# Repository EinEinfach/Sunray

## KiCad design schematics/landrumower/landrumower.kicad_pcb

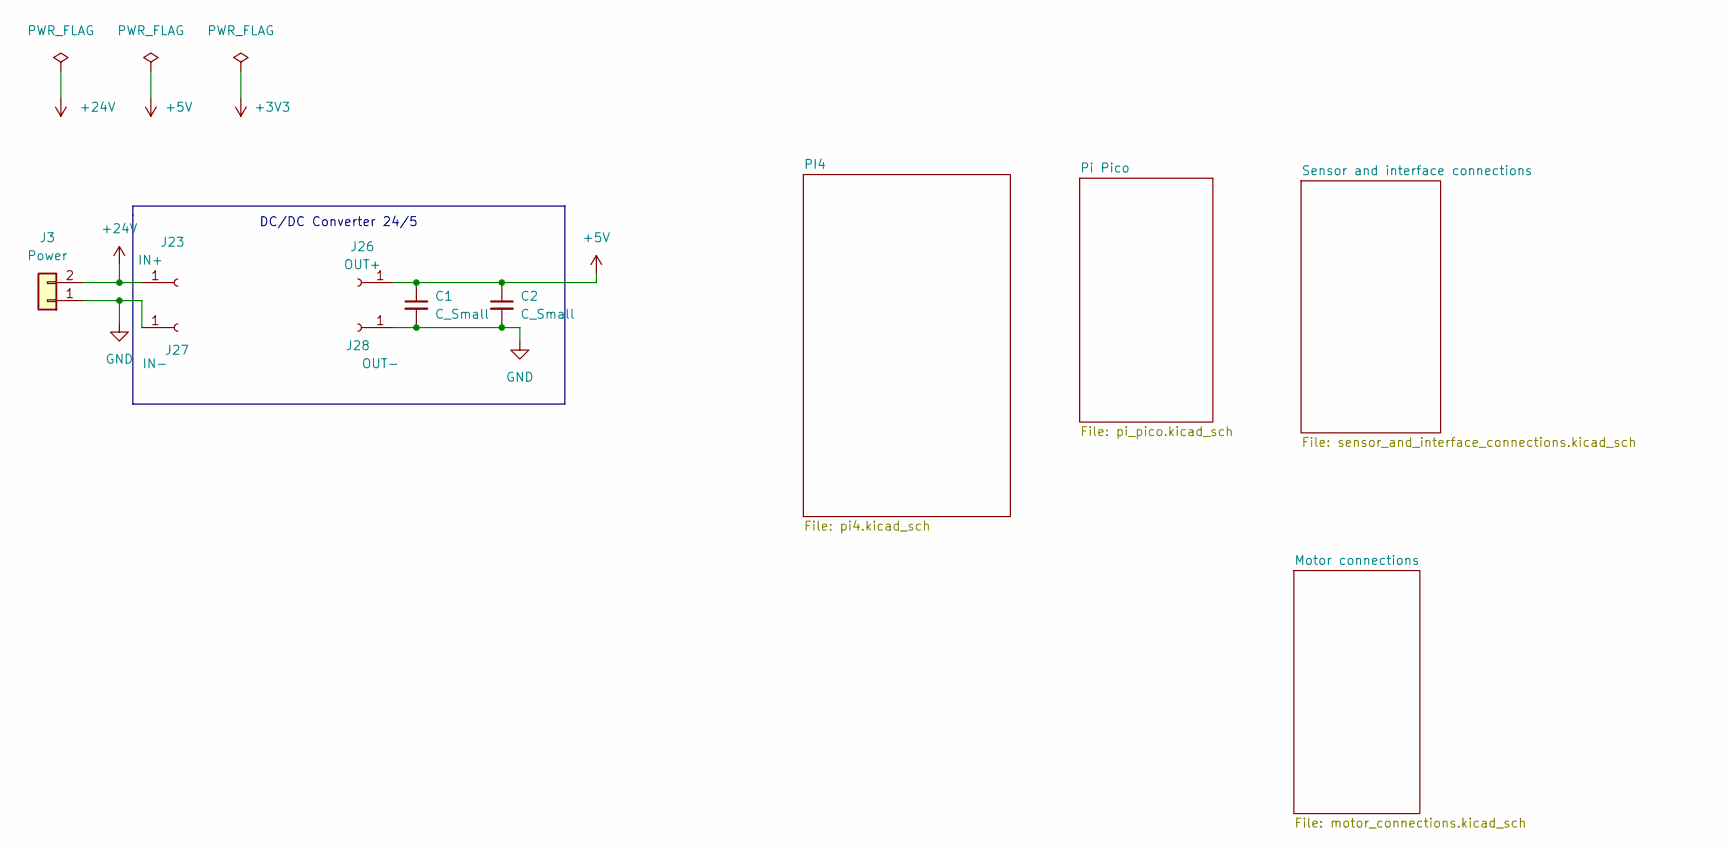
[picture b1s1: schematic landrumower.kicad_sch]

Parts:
C1, C2: C_Small; C_0805_2012Metric_Pad1.18x1.45mm_HandSolder
J3: Power; TerminalBlock_Altech_AK300-2_P5.00mm
J23: IN+; PinSocket_1x01_P2.54mm_Vertical
J26: OUT+; PinSocket_1x01_P2.54mm_Vertical
J27: IN-; PinSocket_1x01_P2.54mm_Vertical
J28: OUT-; PinSocket_1x01_P2.54mm_Vertical

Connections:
+5V: C1.1, C2.1, J26.1; also elsewhere on the board
+24V: J3.2, J23.1
GND: C1.2, C2.2, J3.1, J27.1, J28.1; also elsewhere on the board

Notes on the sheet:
DC/DC Converter 24/5

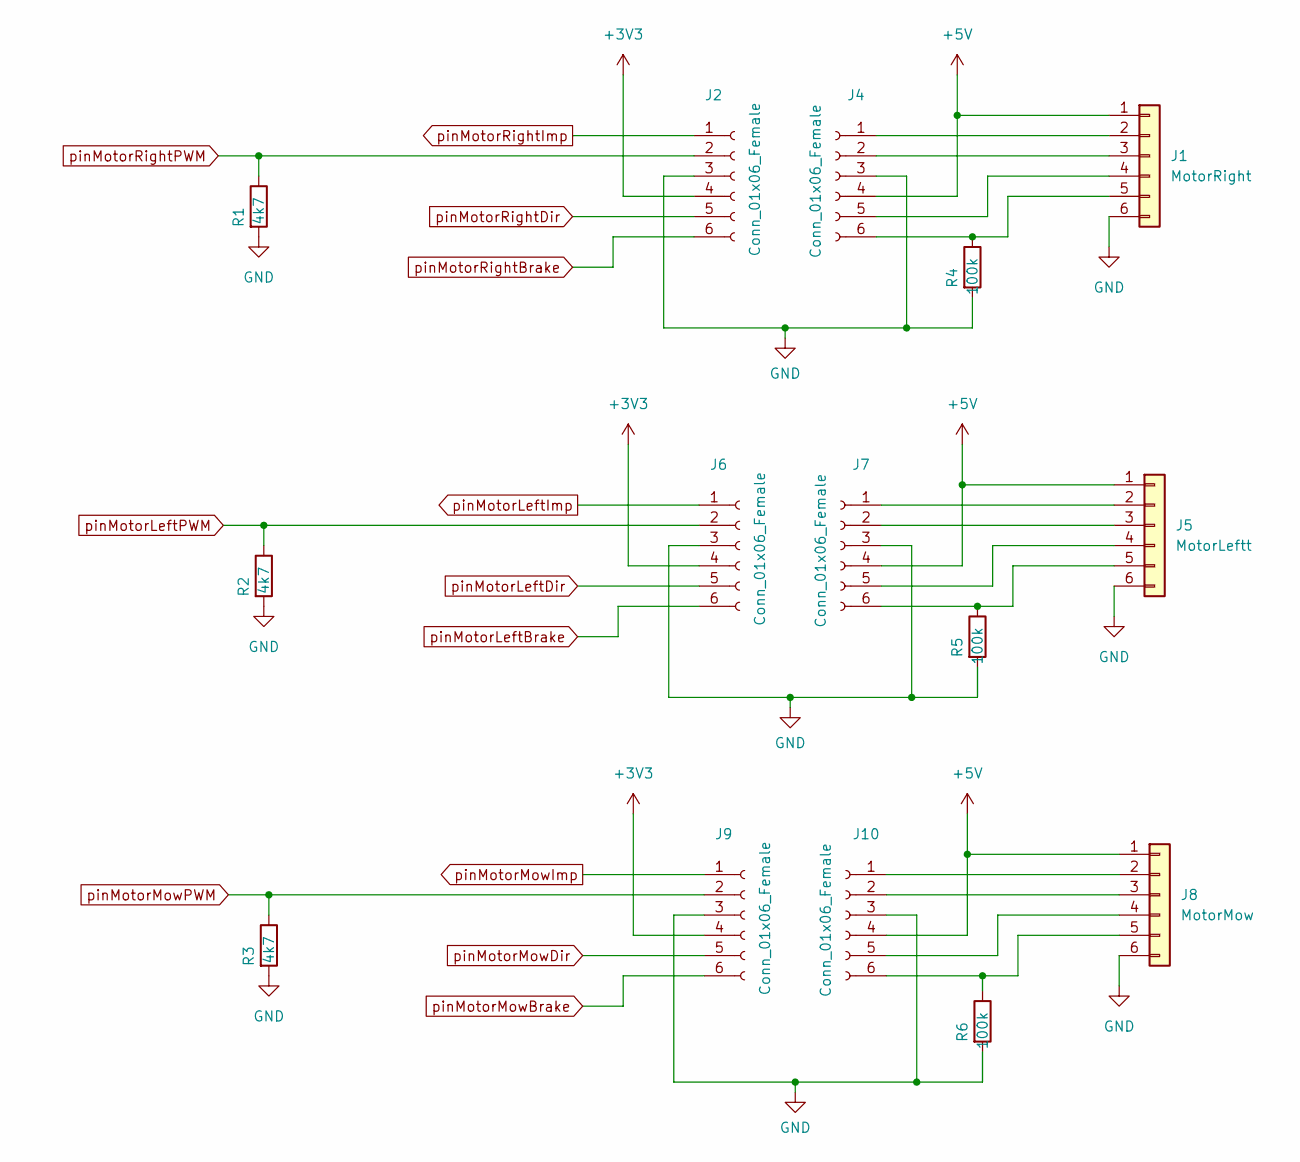
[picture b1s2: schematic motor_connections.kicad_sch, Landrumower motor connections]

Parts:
J1: MotorRight; JST_EH_B6B-EH-A_1x06_P2.50mm_Vertical
J2, J4, J6, J7, J9, J10: Conn_01x06_Female; PinSocket_1x06_P2.54mm_Vertical
J5: MotorLeftt; JST_EH_B6B-EH-A_1x06_P2.50mm_Vertical
J8: MotorMow; JST_EH_B6B-EH-A_1x06_P2.50mm_Vertical
R1, R2, R3: 4k7; R_0805_2012Metric_Pad1.20x1.40mm_HandSolder
R4, R5, R6: 100k; R_0805_2012Metric_Pad1.20x1.40mm_HandSolder

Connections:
+3V3: J2.4, J6.4, J9.4; also elsewhere on the board
+5V: J1.1, J4.4, J5.1, J7.4, J8.1, J10.4; also elsewhere on the board
GND: J1.6, J2.3, J4.3, J5.6, J6.3, J7.3, J8.6, J9.3, J10.3, R1.2, R2.2, R3.2, R4.2, R5.2, R6.2; also elsewhere on the board
unnamed: J1.2, J4.1
unnamed: J1.3, J4.2
unnamed: J1.4, J4.5
unnamed: J1.5, J4.6, R4.1
unnamed: J5.2, J7.1
unnamed: J5.3, J7.2
unnamed: J5.4, J7.5
unnamed: J5.5, J7.6, R5.1
unnamed: J8.2, J10.1
unnamed: J8.3, J10.2
unnamed: J8.4, J10.5
unnamed: J8.5, J10.6, R6.1
pinMotorLeftBrake: J6.6; also elsewhere on the board
pinMotorLeftDir: J6.5; also elsewhere on the board
pinMotorLeftImp: J6.1; also elsewhere on the board
pinMotorLeftPWM: J6.2, R2.1; also elsewhere on the board
pinMotorMowBrake: J9.6; also elsewhere on the board
pinMotorMowDir: J9.5; also elsewhere on the board
pinMotorMowImp: J9.1; also elsewhere on the board
pinMotorMowPWM: J9.2, R3.1; also elsewhere on the board
pinMotorRightBrake: J2.6; also elsewhere on the board
pinMotorRightDir: J2.5; also elsewhere on the board
pinMotorRightImp: J2.1; also elsewhere on the board
pinMotorRightPWM: J2.2, R1.1; also elsewhere on the board

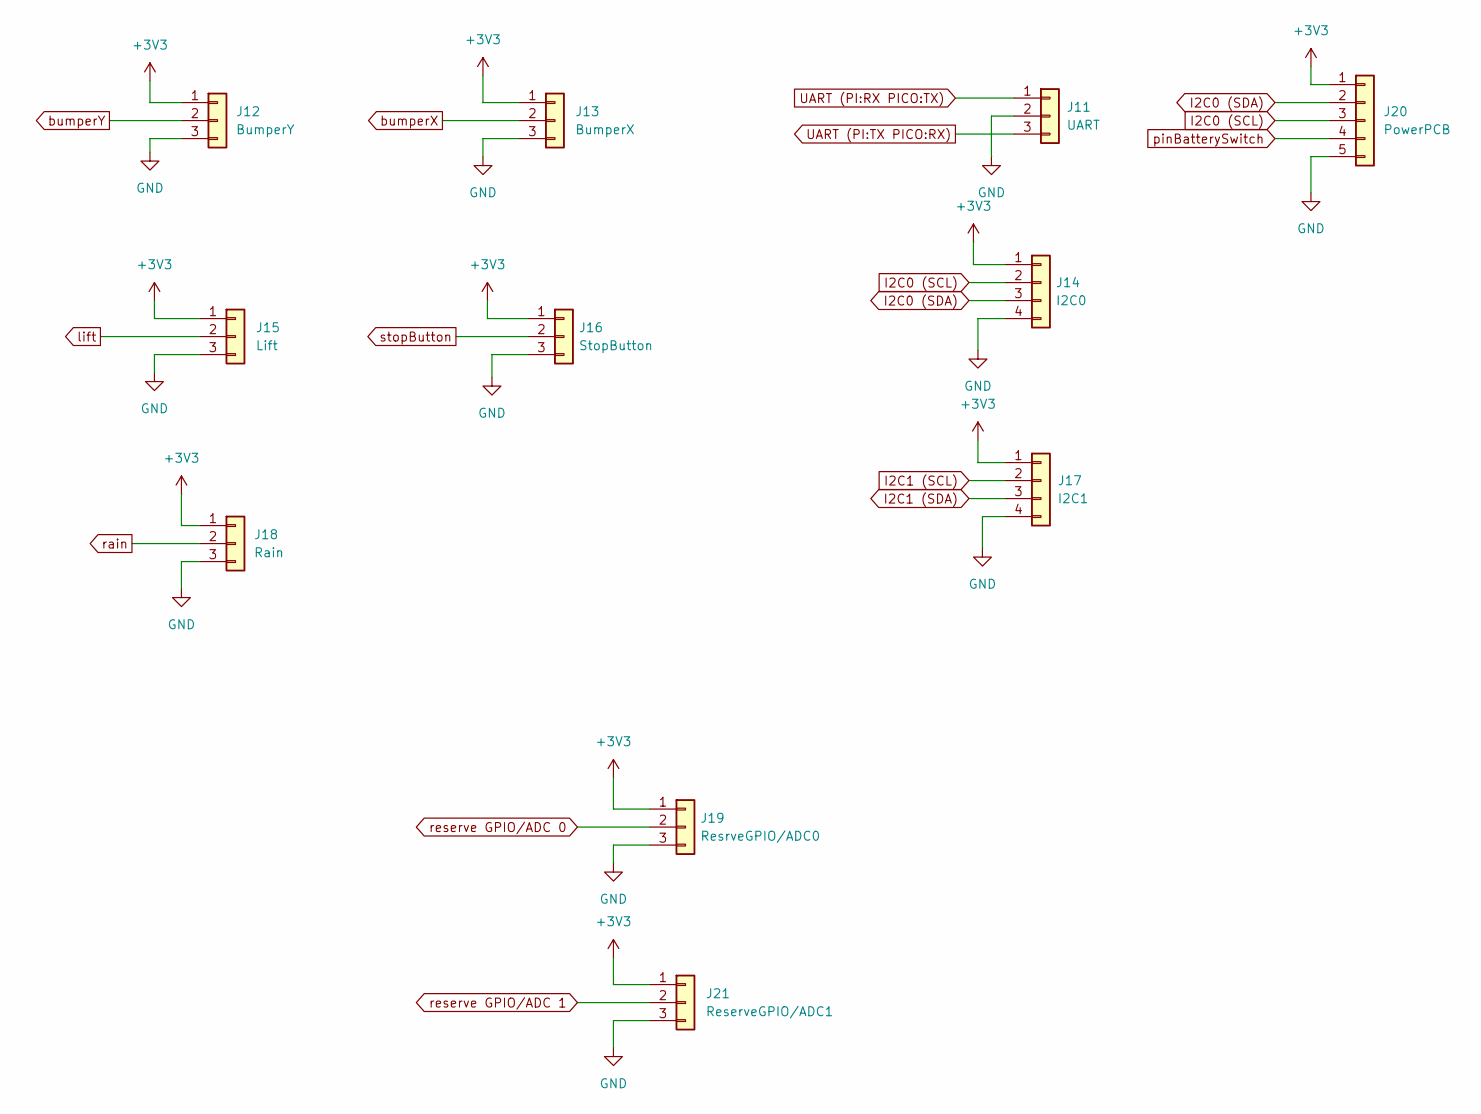
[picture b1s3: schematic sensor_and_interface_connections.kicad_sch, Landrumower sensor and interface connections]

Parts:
J11: UART; JST_EH_B3B-EH-A_1x03_P2.50mm_Vertical
J12: BumperY; JST_EH_B3B-EH-A_1x03_P2.50mm_Vertical
J13: BumperX; JST_EH_B3B-EH-A_1x03_P2.50mm_Vertical
J14: I2C0; JST_EH_B4B-EH-A_1x04_P2.50mm_Vertical
J15: Lift; JST_EH_B3B-EH-A_1x03_P2.50mm_Vertical
J16: StopButton; JST_EH_B3B-EH-A_1x03_P2.50mm_Vertical
J17: I2C1; JST_EH_B4B-EH-A_1x04_P2.50mm_Vertical
J18: Rain; JST_EH_B3B-EH-A_1x03_P2.50mm_Vertical
J19: ResrveGPIO/ADC0; JST_EH_B3B-EH-A_1x03_P2.50mm_Vertical
J20: PowerPCB; JST_EH_B5B-EH-A_1x05_P2.50mm_Vertical
J21: ReserveGPIO/ADC1; JST_EH_B3B-EH-A_1x03_P2.50mm_Vertical

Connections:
+3V3: J12.1, J13.1, J14.1, J15.1, J16.1, J17.1, J18.1, J19.1, J20.1, J21.1; also elsewhere on the board
GND: J11.2, J12.3, J13.3, J14.4, J15.3, J16.3, J17.4, J18.3, J19.3, J20.5, J21.3; also elsewhere on the board
I2C0 (SCL): J14.2, J20.3; also elsewhere on the board
I2C0 (SDA): J14.3, J20.2; also elsewhere on the board
I2C1 (SCL): J17.2; also elsewhere on the board
I2C1 (SDA): J17.3; also elsewhere on the board
UART (PI:RX PICO:TX): J11.1; also elsewhere on the board
UART (PI:TX PICO:RX): J11.3; also elsewhere on the board
bumperX: J13.2; also elsewhere on the board
bumperY: J12.2; also elsewhere on the board
lift: J15.2; also elsewhere on the board
pinBatterySwitch: J20.4; also elsewhere on the board
rain: J18.2; also elsewhere on the board
reserve GPIO/ADC 0: J19.2; also elsewhere on the board
reserve GPIO/ADC 1: J21.2; also elsewhere on the board
stopButton: J16.2; also elsewhere on the board

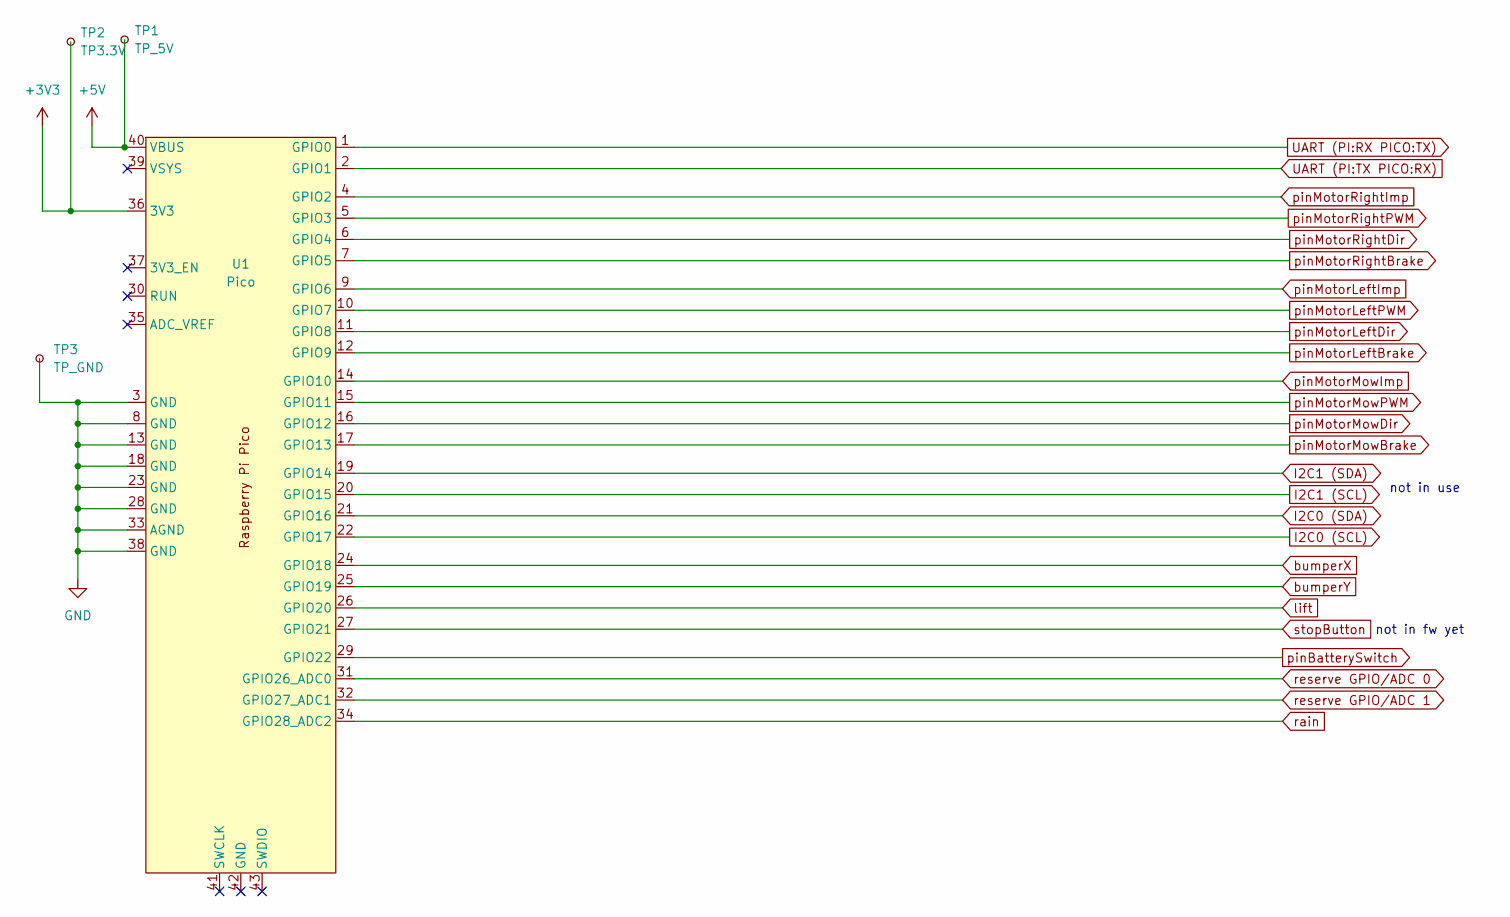
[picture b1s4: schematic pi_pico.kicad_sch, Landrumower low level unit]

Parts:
TP1: TP_5V; TestPoint_Pad_D2.0mm
TP2: TP3.3V; TestPoint_Pad_D2.0mm
TP3: TP_GND; TestPoint_Pad_D2.0mm
U1: Pico; RPi_Pico_SMD_TH

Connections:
+3V3: TP2.1, U1.36 (3V3); also elsewhere on the board
+5V: TP1.1, U1.40 (VBUS); also elsewhere on the board
GND: TP3.1, U1.3 (GND), U1.8 (GND), U1.13 (GND), U1.18 (GND), U1.23 (GND), U1.28 (GND), U1.33 (AGND), U1.38 (GND); also elsewhere on the board
I2C0 (SCL): U1.22 (GPIO17); also elsewhere on the board
I2C0 (SDA): U1.21 (GPIO16); also elsewhere on the board
I2C1 (SCL): U1.20 (GPIO15); also elsewhere on the board
I2C1 (SDA): U1.19 (GPIO14); also elsewhere on the board
UART (PI:RX PICO:TX): U1.1 (GPIO0); also elsewhere on the board
UART (PI:TX PICO:RX): U1.2 (GPIO1); also elsewhere on the board
bumperX: U1.24 (GPIO18); also elsewhere on the board
bumperY: U1.25 (GPIO19); also elsewhere on the board
lift: U1.26 (GPIO20); also elsewhere on the board
pinBatterySwitch: U1.29 (GPIO22); also elsewhere on the board
pinMotorLeftBrake: U1.12 (GPIO9); also elsewhere on the board
pinMotorLeftDir: U1.11 (GPIO8); also elsewhere on the board
pinMotorLeftImp: U1.9 (GPIO6); also elsewhere on the board
pinMotorLeftPWM: U1.10 (GPIO7); also elsewhere on the board
pinMotorMowBrake: U1.17 (GPIO13); also elsewhere on the board
pinMotorMowDir: U1.16 (GPIO12); also elsewhere on the board
pinMotorMowImp: U1.14 (GPIO10); also elsewhere on the board
pinMotorMowPWM: U1.15 (GPIO11); also elsewhere on the board
pinMotorRightBrake: U1.7 (GPIO5); also elsewhere on the board
pinMotorRightDir: U1.6 (GPIO4); also elsewhere on the board
pinMotorRightImp: U1.4 (GPIO2); also elsewhere on the board
pinMotorRightPWM: U1.5 (GPIO3); also elsewhere on the board
rain: U1.34 (GPIO28_ADC2); also elsewhere on the board
reserve GPIO/ADC 0: U1.31 (GPIO26_ADC0); also elsewhere on the board
reserve GPIO/ADC 1: U1.32 (GPIO27_ADC1); also elsewhere on the board
stopButton: U1.27 (GPIO21); also elsewhere on the board

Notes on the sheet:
not in use
not in fw yet

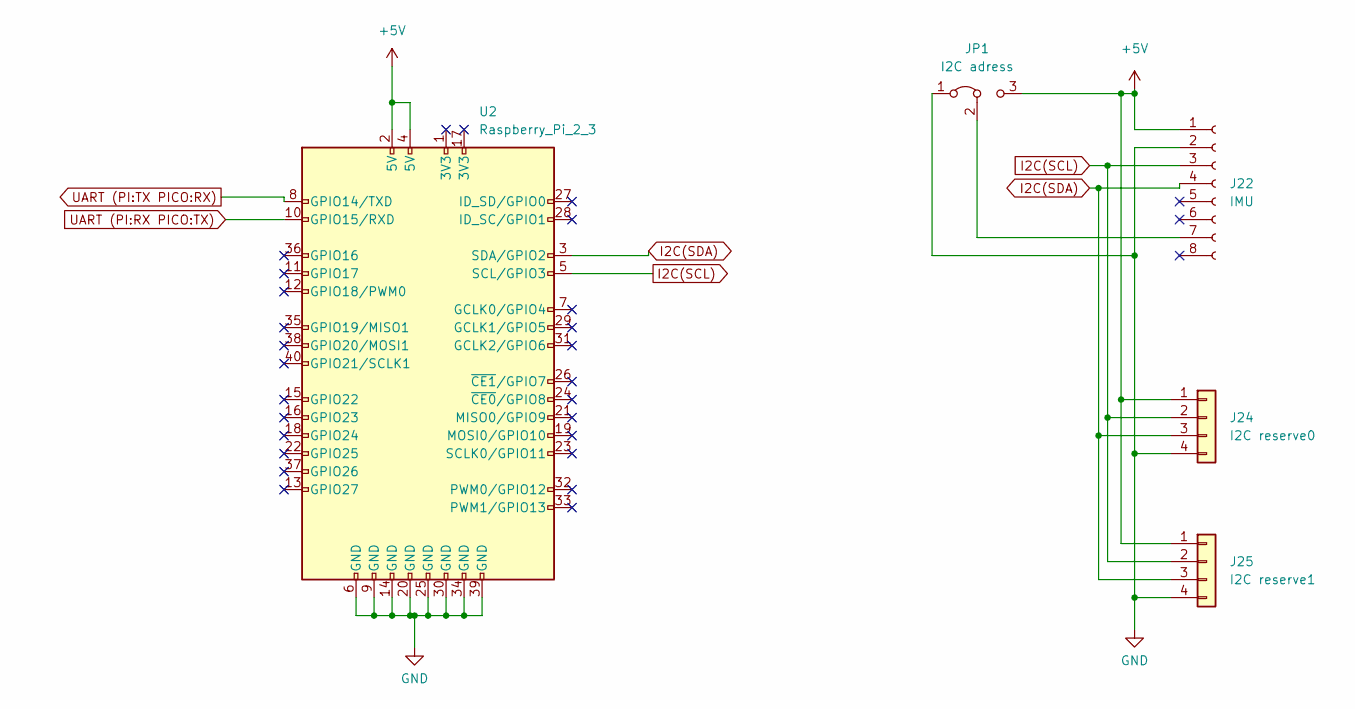
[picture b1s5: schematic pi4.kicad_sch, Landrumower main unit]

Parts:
J22: IMU; PinSocket_1x08_P2.54mm_Vertical
J24: I2C reserve0; JST_EH_B4B-EH-A_1x04_P2.50mm_Vertical
J25: I2C reserve1; JST_EH_B4B-EH-A_1x04_P2.50mm_Vertical
JP1: I2C adress; PinHeader_1x03_P2.54mm_Vertical
U2: Raspberry_Pi_2_3; PinSocket_2x20_P2.54mm_Vertical

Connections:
+3.3VP: U2.1 (3V3), U2.17 (3V3); also elsewhere on the board
+5V: J22.1, J24.1, J25.1, JP1.3 (B), U2.2 (5V), U2.4 (5V); also elsewhere on the board
GND: J22.2, J24.4, J25.4, JP1.1 (A), U2.6 (GND), U2.9 (GND), U2.14 (GND), U2.20 (GND), U2.25 (GND), U2.30 (GND), U2.34 (GND), U2.39 (GND); also elsewhere on the board
GPIO1: U2.27 (ID_SD/GPIO0); also elsewhere on the board
GPIO2: U2.28 (ID_SC/GPIO1); also elsewhere on the board
GPIO4: U2.7 (GCLK0/GPIO4)
GPIO5: U2.29 (GCLK1/GPIO5); also elsewhere on the board
GPIO6: U2.31 (GCLK2/GPIO6); also elsewhere on the board
GPIO13: U2.33 (PWM1/GPIO13); also elsewhere on the board
GPIO19: U2.35 (GPIO19/MISO1); also elsewhere on the board
I2C(SCL): J22.3, J24.2, J25.2, U2.5 (SCL/GPIO3)
I2C(SDA): J22.4, J24.3, J25.3, U2.3 (SDA/GPIO2)
unnamed: J22.7, JP1.2 (C)
UART (PI:RX PICO:TX): U2.10 (GPIO15/RXD); also elsewhere on the board
UART (PI:TX PICO:RX): U2.8 (GPIO14/TXD); also elsewhere on the board

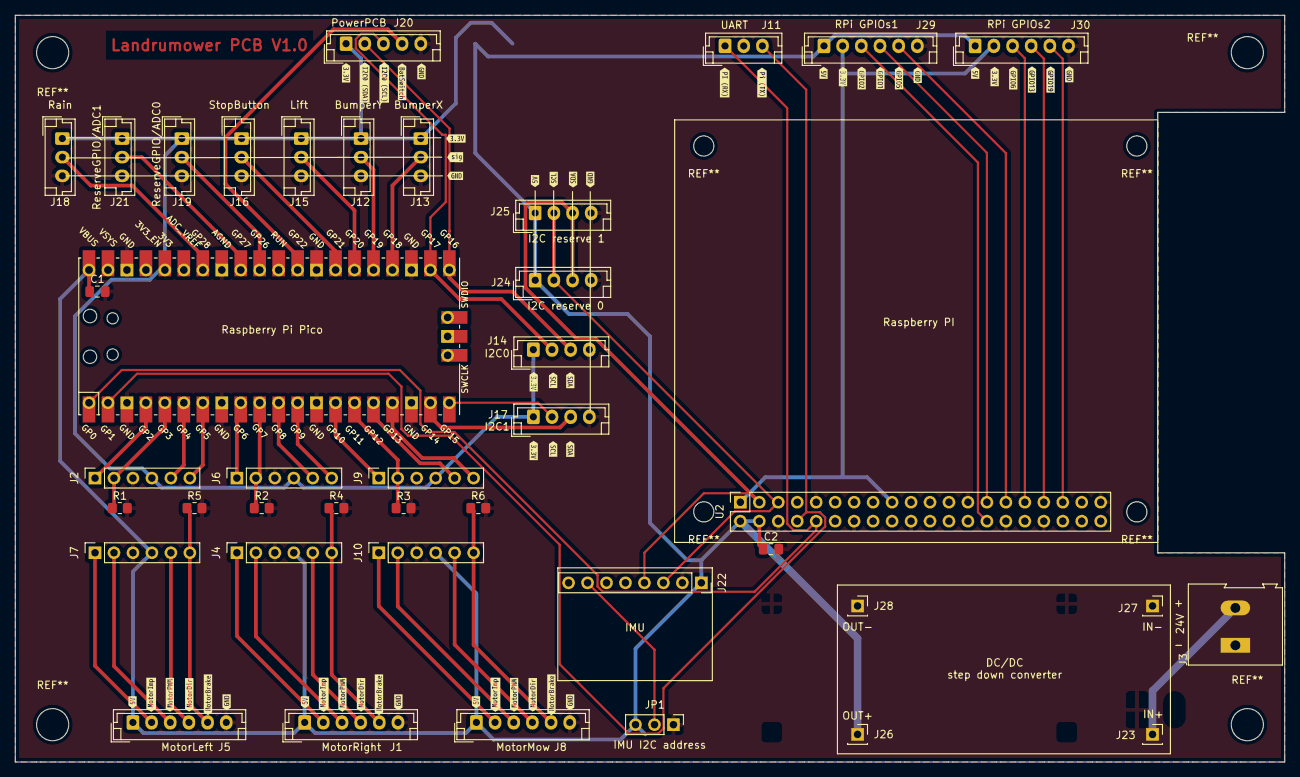
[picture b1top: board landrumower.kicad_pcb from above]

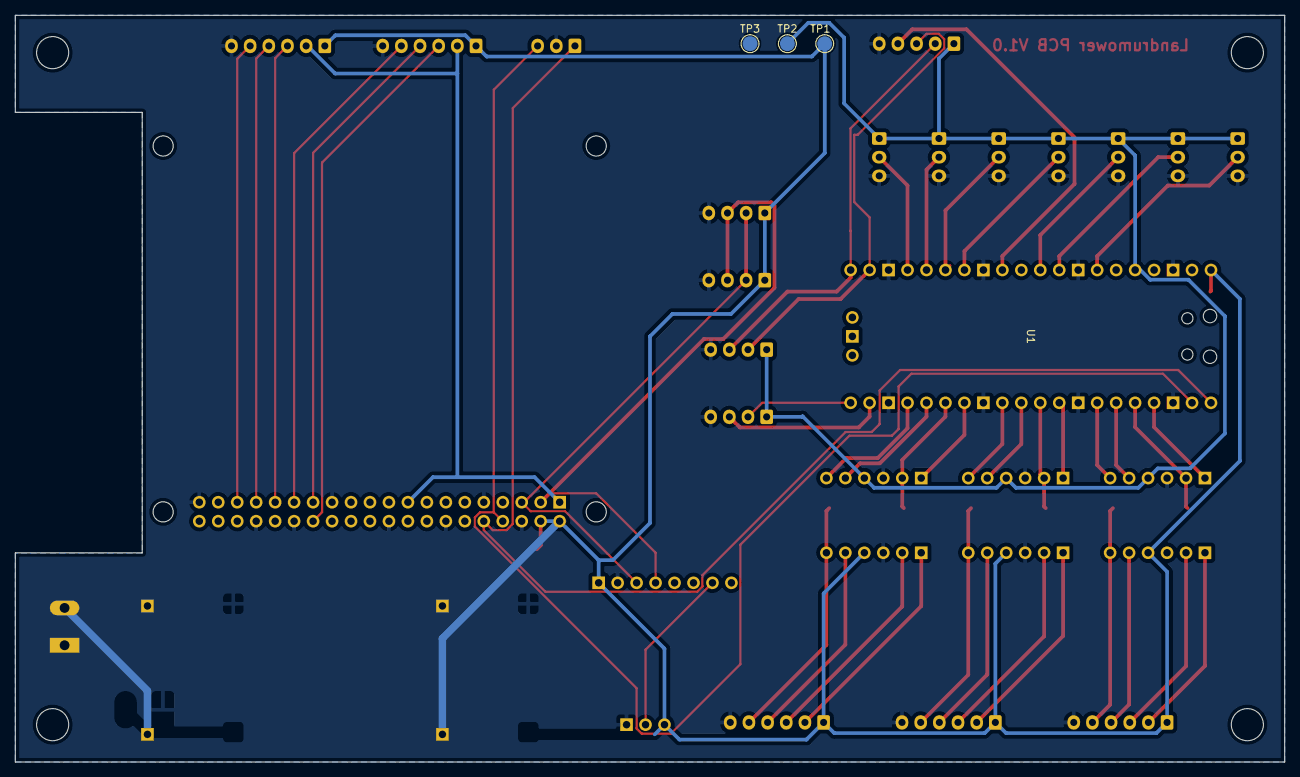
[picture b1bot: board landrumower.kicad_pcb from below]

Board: 2 copper layers, 170.0 x 100.0 mm, 94 parts (3 on the bottom side), 52 nets.

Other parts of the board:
J29: RPI GPIOs1; JST_EH_B6B-EH-A_1x06_P2.50mm_Vertical
J30: RPI GPIOs2; JST_EH_B6B-EH-A_1x06_P2.50mm_Vertical
kibuzzard-65CA0A7B, kibuzzard-65CA0A7B#2, kibuzzard-65CA0A7B#3: G***; kibuzzard-65CA0A7B
kibuzzard-65CA0AF1, kibuzzard-65CA0AF1#2, kibuzzard-65CA0AF1#3: G***; kibuzzard-65CA0AF1
kibuzzard-65CA0B61, kibuzzard-65CA0B61#2: G***; kibuzzard-65CA0B61
kibuzzard-65CA0BDD: G***; kibuzzard-65CA0BDD
kibuzzard-65CA0BE5, kibuzzard-65CA0BE5#2, kibuzzard-65CA0BE5#3: G***; kibuzzard-65CA0BE5
kibuzzard-65CA0CDE, kibuzzard-65CA0CDE#2, kibuzzard-65CA0CDE#3: G***; kibuzzard-65CA0CDE
kibuzzard-65CA0D25, kibuzzard-65CA0D25#2, kibuzzard-65CA0D25#3: G***; kibuzzard-65CA0D25
kibuzzard-65CA1A09: G***; kibuzzard-65CA1A09
kibuzzard-65CA13E2: G***; kibuzzard-65CA13E2
kibuzzard-65CA15BA: G***; kibuzzard-65CA15BA
kibuzzard-65CA15CC: G***; kibuzzard-65CA15CC
kibuzzard-65CA15DA: G***; kibuzzard-65CA15DA
kibuzzard-65CA18B9, kibuzzard-65CA18B9#2: G***; kibuzzard-65CA18B9
kibuzzard-65CA18EE, kibuzzard-65CA18EE#2: G***; kibuzzard-65CA18EE
kibuzzard-65CA19E7: G***; kibuzzard-65CA19E7
kibuzzard-65CA19F9: G***; kibuzzard-65CA19F9
kibuzzard-65CA34CF: G***; kibuzzard-65CA34CF
kibuzzard-65CA34D8: G***; kibuzzard-65CA34D8
kibuzzard-65CA36D0: G***; kibuzzard-65CA36D0
kibuzzard-65CA137E, kibuzzard-65CA137E#2, kibuzzard-65CA137E#3: G***; kibuzzard-65CA137E
kibuzzard-65CA190F: G***; kibuzzard-65CA190F
kibuzzard-65CA191B: G***; kibuzzard-65CA191B
kibuzzard-65CA193C, kibuzzard-65CA193C#2: G***; kibuzzard-65CA193C
kibuzzard-65CA369C: G***; kibuzzard-65CA369C
kibuzzard-65CA1367, kibuzzard-65CA1367#2: G***; kibuzzard-65CA1367
kibuzzard-65CA1392, kibuzzard-65CA1392#2, kibuzzard-65CA1392#3: G***; kibuzzard-65CA1392
kibuzzard-65CA1528: G***; kibuzzard-65CA1528
kibuzzard-65CA1927: G***; kibuzzard-65CA1927
kibuzzard-65CA3687: G***; kibuzzard-65CA3687
kibuzzard-65CA3704: G***; kibuzzard-65CA3704
kibuzzard-65CA3716: G***; kibuzzard-65CA3716

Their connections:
+3.3VP: J29.2, J30.2; also elsewhere on the board
+5V: J29.1, J30.1; also elsewhere on the board
GND: J29.6, J30.6; also elsewhere on the board
GPIO1: J29.4; also elsewhere on the board
GPIO2: J29.3; also elsewhere on the board
GPIO5: J29.5; also elsewhere on the board
GPIO6: J30.3; also elsewhere on the board
GPIO13: J30.4; also elsewhere on the board
GPIO19: J30.5; also elsewhere on the board

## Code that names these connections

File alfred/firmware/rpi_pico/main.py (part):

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pinLift1 = Pin(20, Pin.IN, Pin.PULL_DOWN)
pinBumperX = Pin(18, Pin.IN, Pin.PULL_DOWN)
pinBumperY = Pin(19, Pin.IN, Pin.PULL_DOWN)
pinBatterySwitch = Pin(22, Pin.OUT)
pinStopButton = Pin(21, Pin.IN, Pin.PULL_UP)
# pinChargeV = ADC(Pin(26))

pinMotorRightImp = Pin(2, Pin.IN)
pinMotorRightPWM = PWM(Pin(3))
pinMotorRightDir = Pin(4, Pin.OUT)
pinMotorRightBrake = Pin(5, Pin.OUT)

pinMotorLeftImp = Pin(6, Pin.IN)
pinMotorLeftPWM = PWM(Pin(7))
pinMotorLeftDir = Pin(8, Pin.OUT)
pinMotorLeftBrake = Pin(9, Pin.OUT)

pinMotorMowImp = Pin(10, Pin.IN)
pinMotorMowPWM = PWM(Pin(11))
pinMotorMowDir = Pin(12, Pin.OUT)
pinMotorMowBrake = Pin(13, Pin.OUT)

# activate debug
DEBUG = False
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motorMowTicksTimeout = time.ticks_ms()
stopButtonTimeout = time.ticks_ms()

stopButton = 0

batVoltage = 0
batVoltageLP = 0
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mowSpeedSet = 0
motorOverload = False
motorMowFault = False
bumperX = 0
bumperY = 0
liftLeft = 0
liftRight = 0
rain = 65535
rainLP = 65535
raining = 0
lift = 0
bumper = 0
ovCheck = 0 
enableTractionBrakesLeft = False
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    global motorMowTicksTimeout
    global odomTicksMow

    if pinMotorMowImp.value() == 0: return
    if time.ticks_diff(motorMowTicksTimeout, time.ticks_ms()) > 0: return
    motorMowTicksTimeout = time.ticks_add(time.ticks_ms(), 1)
    odomTicksMow += 1
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    global motorLeftTicksTimeout
    global odomTicksLeft

    if pinMotorLeftImp.value() == 0: return
    if time.ticks_diff(motorLeftTicksTimeout, time.ticks_ms()) > 0: return
    motorLeftTicksTimeout = time.ticks_add(time.ticks_ms(), 1)
    odomTicksLeft += 1
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    global motorRightTicksTimeout
    global odomTicksRight

    if pinMotorRightImp.value() == 0: return
    if time.ticks_diff(motorRightTicksTimeout, time.ticks_ms()) > 0: return
    motorRightTicksTimeout = time.ticks_add(time.ticks_ms(), 1)
    odomTicksRight += 1
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        if time.ticks_diff(mowBrakeStateTimout,time.ticks_ms()) <= 0:
            mowBrakeStateTimout = time.ticks_add(time.ticks_ms(), 1000)
            if mowSpeedSet >= 0:
                pinMotorMowDir.value(1)
            else:
                pinMotorMowDir.value(0)
            if mowBrakeState >= 3:
                pinMotorMowPWM.freq(FREQ_MOW)
                pinMotorMowPWM.duty_u16(int((abs(mowSpeedSet)*65535)/255))
            if mowBrakeState < 20:
                mowBrakeState += 1
    else:
        mowBrakeStateTimout = time.ticks_ms()
        mowBrakeState = 0
        pinMotorMowPWM.freq(FREQ_MOW)
        pinMotorMowPWM.duty_u16(0)
        pinMotorMowBrake.value(1)

# 0 = off, 255 = full speed
def motor() -> None:
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    
    # left traction motor
    if leftSpeedSet <= 0:
        pinMotorLeftDir.value(0)
    else:
        pinMotorLeftDir.value(1)
    pinMotorLeftBrake.value(int(enableTractionBrakesLeft))
    pinMotorLeftPWM.freq(FREQ)
    pinMotorLeftPWM.duty_u16(int((abs(leftSpeedSet)*65535)/255))

    # right traction motor
    if rightSpeedSet <= 0:
        pinMotorRightDir.value(1)
    else:
        pinMotorRightDir.value(0)
    pinMotorRightBrake.value(int(enableTractionBrakesRight))
    pinMotorRightPWM.freq(FREQ)
    pinMotorRightPWM.duty_u16(int((abs(rightSpeedSet)*65535)/255))

def readSensorHighFrequency() -> None:
    global chgVoltage
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
    # rain 
    w = 0.99
    rain = pinRain.read_u16()
    rainLP = w * rainLP + (1 - w) * rain
    raining = int((((rainLP * 100) / 65535) < 50))

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    lift = int(liftLeft or liftRight)

    # bumper
    bumperX = pinBumperX.value()
    bumperY = pinBumperY.value()
    bumper = int(bumperX or bumperY)

    # stop button
    if pinStopButton.value() == 1:
        stopButton = 1
    else:
        stopButton = 0

    # dummys
    batteryTemp = 20 
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        else:
            print("Battery oltage critical level reached")
            print("SHUTTING DOWN")
            pinBatterySwitch.value(0)
    if switchBatteryDebounceCtr > 40:
        print(f"SHUTTING DOWN")
        pinBatterySwitch.value(0)
    
# request motor
# AT+M,20,20,1
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def cmdResetMotorFaults() -> None:
    if DEBUG:
        print("Motor faults request. Reseting drivers")
    pinMotorRightPWM.duty_u16(0) 
    pinMotorRightDir.value(0) 
    pinMotorRightBrake.value(0)  

    pinMotorLeftPWM.duty_u16(0)
    pinMotorLeftDir.value(0)  
    pinMotorLeftBrake.value(0)
    s = f"R"
    cmdAnswer(s)
    sleep_ms(200)
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wdt = WDT(timeout=6000) 

# swicht on battery
pinBatterySwitch.value(1)

# define here setup debug outputs
if DEBUG2:
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        print(f"Found devices on I2C bus: {hex(device)}")

# set ISRs
pinMotorMowImp.irq(trigger=Pin.IRQ_RISING, handler=OdometryMowISR)
pinMotorLeftImp.irq(trigger=Pin.IRQ_RISING, handler=OdometryLeftISR)
pinMotorRightImp.irq(trigger=Pin.IRQ_RISING, handler=OdometryRightISR)

# main loop
while True:
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
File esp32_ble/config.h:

/*
  ESP32 firmware providing:
     1. BLE UART bridge (GATT server UART)
     2. WiFi UART bridge (HTTP server UART)


  Steps to install ESP32 for Arduino IDE:
     1. Arduino IDE: File->Preferences:  Add to board manager URLs: ",https://dl.espressif.com/dl/package_esp32_index.json"
     2. Choose "Tools->Board->Boards Manager"
     3. Add board "esp32" (IMPORTANT!!! choose v1.0.4, latest v1.0.6 does not seem to connect to WiFi access point! )
     4. Choose Board "ESP32 Dev Module"  (if upload does not work: PRESS EN+BOOT, release EN  on your ESP32)
     5. Choose Partition Scheme "Minimal SPIFFS"  (otherwise you may get 'memory space errors' in the Arduino IDE)
    (also see: https://github.com/espressif/arduino-esp32/blob/master/docs/arduino-ide/boards_manager.md )
     6. Choose Port (Windows NOTE: if the port is not shown you may have to install drivers: https://www.silabs.com/developers/usb-to-uart-bridge-vcp-drivers)
     7. Choose "Tools->Manager Libraries..."
     8. Add library "ESP32_HTTPS_Server by Frank Hessel"  
     9. Add library "ArduinoJson by Benoit Blanchon" and "ThingsOfValue SDK for Arduino"
     10. Add library "NimBLE-Arduino by h2zero"  (requires less memory - only used if activated 'USE_NIM_BLE')
     11. Copy this file into 'config.h'     
     12. Configure the options below and finally compile and upload this project.
     

  wiring (also see wiring image in Github folder):
  ESP32 Rx2 (GPIO16) ---  Ardumower PCB1.3 Bluetooth conn RX   (3.3v level)
  ESP32 Tx2 (GPIO17) ---  Ardumower PCB1.3 Bluetooth conn TX   (3.3v level)
  ESP32 GND          ---  Ardumower PCB1.3 Bluetooth conn GND
  ESP32 5V  (Vin)    ---  Ardumower PCB1.3 Bluetooth conn 5V


  Note: ESP32 D1 Mini (china cheapo) can work as a comm/BLE chip.
  Data is reported and mower can be steered using app.
  Things to remember are:
  - need to wait few secs after mower reboots before connecting (CRC issues)
  - need to close/reopen app if the phone disconnects (CRC issues)

  Note: Please see and ask in the forum if you experience HTTP connection issues: 
  https://forum.ardumower.de/threads/sunray-app-connection-issue-solved-sunray-app-verbindungsproblem-gel%C3%B6st.24467/

  NOTE: If your ESP32 is not available as a device, you may have to install an USB driver: 
  https://www.silabs.com/developers/usb-to-uart-bridge-vcp-drivers 

*/

#define NAME "Krobi"

// bluetooth low energy (BLE)
#define USE_BLE 1    // comment this line to remove BLE support
#define BLE_MTU 20   // max. transfer bytes per BLE frame
#define BLE_MIN_INTERVAL 2    // connection parameters (tuned for high speed/high power consumption - see: https://support.ambiq.com/hc/en-us/articles/115002907792-Managing-BLE-Connection-Parameters)
#define BLE_MAX_INTERVAL 10
#define BLE_LATENCY      0
#define BLE_TIMEOUT      30  
//#define USE_NIM_BLE   1 // use NimBLE library (requires less memory) instead of ESP32 library? 

//IP WiFi:
#define WIFI_STATIC_IP true  // activate this for static IP
//#define WIFI_STATIC_IP false // activate this for dynamic IP
// if using static IP, configure IPs below
#define WIFI_STATIC_IP_LOCAL  192,168,2,55
#define WIFI_STATIC_IP_GW     192,168,2,1
#define WIFI_STATIC_IP_SUBNET 255,255,255,0
#define WIFI_STATIC_IP_DNS1   192,168,2,1
#define WIFI_STATIC_IP_DNS2   192,168,2,1

#define WIFI_STA_SSID   "Your WiFi SSID"      // WiFi SSID      (leave empty ("") to not use WiFi)
#define WIFI_STA_PSK    "Your WiFi Password"  // WiFi password  (leave empty ("") to not use WiFi)
#define WIFI_TIMEOUT_FIRST_RESPONSE  800   // fast response times (500), for more reliable choose: 800     
#define WIFI_TIMEOUT_RESPONSE        400   // fast response times (100), for more reliable choose: 400

// comment this line to use HTTP, uncomment to use HTTPS
// NOTE: if using HTTPS, you also need to uncomment USE_NIM_BLE above!
//#define USE_HTTPS  1  


// Relay server
//
// Install this library with the Arduino Library Manager:
// ArduinoWebsockets - by Gil Maimon - https://github.com/gilmaimon/ArduinoWebsockets
//
//#define USE_RELAY
//#define RELAY_URL       "wss://example.relay.mow.timotto.io/mower"
//#define RELAY_USERNAME  ""
//#define RELAY_PASSWORD  ""
//#define RELAY_TIMEOUT   1000
//#define RELAY_PINGWAIT  55

// MQTT server 
// (subscribed topcis: '/command/start', '/command/stop', '/command/dock')
//  published topics: '/online', '/state', '/props')

#define USE_MQTT  1     // uncomment to activate MQTT
#define MQTT_PREFIX     ""
#define MQTT_HOSTNAME   "192.168.1.10"  // IP or hostname (example: "192.168.1.10")
#define MQTT_PORT       1883
#define MQTT_CLIENT_ID  NAME
#define MQTT_USERNAME   "Your MQTT User Name"
#define MQTT_PASSWORD   "Your MQTT Password"

#define ENCRYPTION_PASSWORD   123456
#define ENCRYPTION_ENABLED    true

// pin assignment
#define pinGpioRx   16    // UART2 / GPIO16 / IO16
#define pinGpioTx   17    // UART2 / GPIO17 / IO17

//#define pinGpioRx   9   // UART1 / GPIO9  / SD2
//#define pinGpioTx   10  // UART1 / GPIO10 / SD3

//#define pinGpioRx   3   // UART0 / GPIO3  / RXD0
//#define pinGpioTx   1   // UART0 / GPIO1  / TXD0

#define pinLED   2

#define CONSOLE Serial  // where to send/receive console messages for debugging etc.
#define UART Serial2    // where to send/receive UART data

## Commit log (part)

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2023-06-13 Changes from 1.0.298 (2022)
2023-06-13 Change gitignore to add config.h to repository. - Added copy of config_example.h as config.h
2023-06-13 config.h for Landrumower (2022): - new bumper trigger delay 100ms
2023-06-26 asm("dsb"); in AmRobotDriver.cpp
2023-06-30 Comment SUPER_SPIKE_ELIMINATOR
2023-08-18 Change data type in point data class
2023-08-27 config.h for 1.0.314 FW
2023-09-19 Change Rain Input Pin to PULLUP
2024-01-31 Inital upload: - fw for rpi pico - changes in sunray fw for running without alfred io-board - config.h for landurmower with pid values and tick per rev
2024-01-31 Schematics rpi_pico
2024-01-31 Added rain calculation to rpi pico fw
2024-02-05 Added undervoltage schutdown logic
2024-02-06 Update schematics for landrumower pcb
2024-02-09 Some changes in battery charging logic
2024-02-12 PCB changes for Landrumower
2024-02-12 Update schematics
2024-02-13 changes in schematics
2024-02-16 Changed raining logic in MCU fw Add rain sensor test to AT+F command
2024-02-19 Added stop button logic
2024-02-20 Changed pin input to pull down for bumpers
2024-02-20 Changed pin input for lift
2024-03-08 Start issue if i2c not available
2024-03-20 Changed rain logic from high to low
2024-05-08 onObstacleRotation same behavior in DockOp
2024-05-31 config.h for landrumower for new fw
2024-06-18 Fix issue with battery charge
2024-08-01 Bug fix charger connected logic
2024-08-02 Changed config for landrualfred
2024-09-08 Possible use of 10mOhm shunt inas
2024-09-09 Back to previous version
2025-03-17 Driver reset from sunray (AT+R)
2025-03-20 - Bypass i2c in rpi pico for standalone testing - Reorganized files for landrumower
2025-03-20 Non blocking motor fault reset
2025-03-20 deactivate hil
2025-03-20 Bumper delay 300ms
2025-03-20 - Initial commit for lcd support
2025-03-21 - Refactoring motor driver recovery function - Added lcd message about recovery for better debugging
2025-03-21 Forgot ver nr from last commit
2025-03-23 Bug fix in motor direction control
2025-03-24 - Trying to fix driver recovery. Reduced overload current for gear motors. - Move lib files to lib folder
2025-03-24 - Fix in motor driver recovery logic - Lcd message support from sunray
2025-03-24 - Send rover state in AT+S message to low level MCU
2025-03-24 Fix include path to op.h
2025-03-24 Switch to stateOpText in serial robot driver to sending state messages to low level mcu
2025-03-24 Fix AT+S command in serial robot driver
2025-03-24 Fill up lcd columns with spaces to remove old message
2025-03-24 - Switch to activeOp->name() call to get current state and forward it to low level mcu
2025-03-24 Replace ljust method, due to missing it in micropython
2025-03-25 Move display print out calc to second core
2025-03-25 Switch to int value as sunray state to low leve mcu over AT+S command
2025-03-25 Fix robot.cpp
2025-03-25 Replace switch statement thorw if statement in robot.cpp
2025-03-25 Fix issue with ol characters on display
2025-03-25 Add to AT+C command new Feature: dockAfterFinish
2025-03-25 AT+C compatibility to Sunray 1.0.324
2025-03-26 - Reset str2str from sunray - Ignore gps in dock state
2025-03-26 Added findings.txt to schematics folder
2025-03-26 Correction in motor overload handling
2025-03-26 Fix AT+C cmd for go to
2025-03-27 Tune motor parameters with AT+CM command
2025-03-27 Motor control test
2025-03-27 Motor control test (AT+E2)
2025-03-28 config landrumower
2025-03-28 config.h landrumower
2025-03-29 More console outputs in case of gps no motion
2025-03-31 - Spikes elimination (1000Hz -> 333Hz) - Update findings file
2025-03-31 Missing ver nur from last commit
2025-04-01 Change overload current to bypass overload detection
2025-04-06 Right and left speed for SerialRobotDriver
2025-04-06 Right and left speed for serial robot driver
2025-04-07 EXPERIMENTAL - New motor control approach wit pid control on pico - Rewrite whole code and ordered it new in classes
2025-04-08 - Fix crashing program if invalid value in process console appear - Trying new parameters für pid
2025-04-08 - Added .gitignore file
2025-04-08 - Added config.h for esp32
2025-04-08 - Changes in Buzzer.cpp to get sound from Landrumower
2025-04-08 Changes in comm.cpp to avoid error with getOpChain
2025-04-08 - Added Landrumower config.h
2025-04-08 - Changed data type of px and py to increase performance of mapCRC calculation
2025-04-08 - Decrease IMU error threshold due to often IMU trigger errors on rotations - Remove SerialRobotDriver.cpp and SerialRobotDriver.h to allow compiling on raspberry pi
2025-04-08 - Changes on AmRobotDriver.cpp to get working JYQD2021 drivers, bumpers and lift sensors on Laundrumower
2025-04-08 - Increase retouching speed if loosing charge connections
2025-04-08 - onObstacleRotation triggers error after mow job finished (due to long path planner calculation?) - Workaround at the moment to set escapeReverseOperation to avoid force error -> Need deeper investi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
2025-04-08 - Some stuff from master branch commit
2025-04-08 - Intergration PR 166 Ability to supress docking after mowing
2025-04-08 Update gitignore
2025-04-09 - Bug fix in motor class (wrong init of pid object) - PID parameters could be wrapped for testing in AT+S message
2025-04-09 - AT+CM command chages PID parameters and wrapped it additionaly once in AT+S message to MCU (usefull if PICO PID controller is used)
2025-04-09 Switch of HIL for mower testing (no changes on CODE)
2025-04-09 AT+CM command chages PID parameters and wrapped it additionaly once in AT+S message to MCU (usefull if PICO PID controller is used)
2025-04-09 Don't reset pid if requested speed == 0 and current speed != 0
2025-04-11 - Change INFO and DEBUG to nonblocking - PID reset in case of direction change - Rain sensor fix init value
2025-04-12 Debug message for AT+M cmd, not for productive
2025-04-12 Remove debug message from SerialRobotDriver
2025-04-12 Change serial baud rate for SerialRobot comunication
2025-04-13 - Change serial robot baudrate to 115200 - Reduce uart timeout in pico fw from 10ms to 5ms
2025-04-13 Added version number to main.py. Missing in las commit
2025-04-16 switch off watchdog for testing purpose
2025-04-20 - OTA ability - Add deploy.sh script - move last main.py without classes to firmware_archive folder
2025-04-22 remove cmd to exit infinity loop
2025-04-22 Change rSpeed and lSpeed for pico control to int values
2025-04-22 Added http server changes from origin branch
2025-04-22 Added .gitignore
2025-04-22 Landrumower config for new fw
2025-04-22 Dummy left and right speed for canRobotDriver to avoid compiling error
2025-04-22 Missing config values for new fw
2025-04-23 rSpeedForRpm and lSpeedForRpm
2025-04-23 - Fix pwm mode - new deploy.sh - keymaps.lua
2025-04-23 Change kP and kI paramerers to try sunray pid
2025-04-28 - Buzzer support - Many changes in motor.py - move most of configuration labels to main.py
2025-04-30 - Many debug messages in landrumower pico fw - Switch from float arithmetic to int arithmetic in most cases - rspeed and leftspped should be sent in mm/s to landrumower pico fw - Move some read senso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
2025-04-30 Switch off HIL mode from last commit
2025-04-30 Reinit I2C
2025-04-30 Move sensore measure to main loop
2025-04-30 Bug fix in print second loop
2025-05-01 - Reorganize firmware folder - Giving up to increase performance of fw 2.x switch to c++ - Starting to rewriting fw code in c++ (fw 3.x)
2025-05-01 - Work progress on version 3
2025-05-02 Work progress on version 3
2025-07-29 Switch to 18V Makita akku
2025-07-30 Adjust battery undervoltage protection for 18 V Makita battery
2025-07-30 Max number of obstacles added before clearObstacles called
2025-07-30 Change obstacle clear logic
2025-08-06 Change go home voltage
2025-08-06 Deep copy of obstacle polygons on target reached
2025-08-06 Restore from obstaclesCpy on addObstacle
2025-08-06 Correction of restoring obstacles
2025-08-06 New logic to restore old obstacles after triggerin an obstacle, to use path finder fro a to b in right way
2025-08-06 Increase max number of obstacles to restore
2025-08-09 Increase batt full voltage
